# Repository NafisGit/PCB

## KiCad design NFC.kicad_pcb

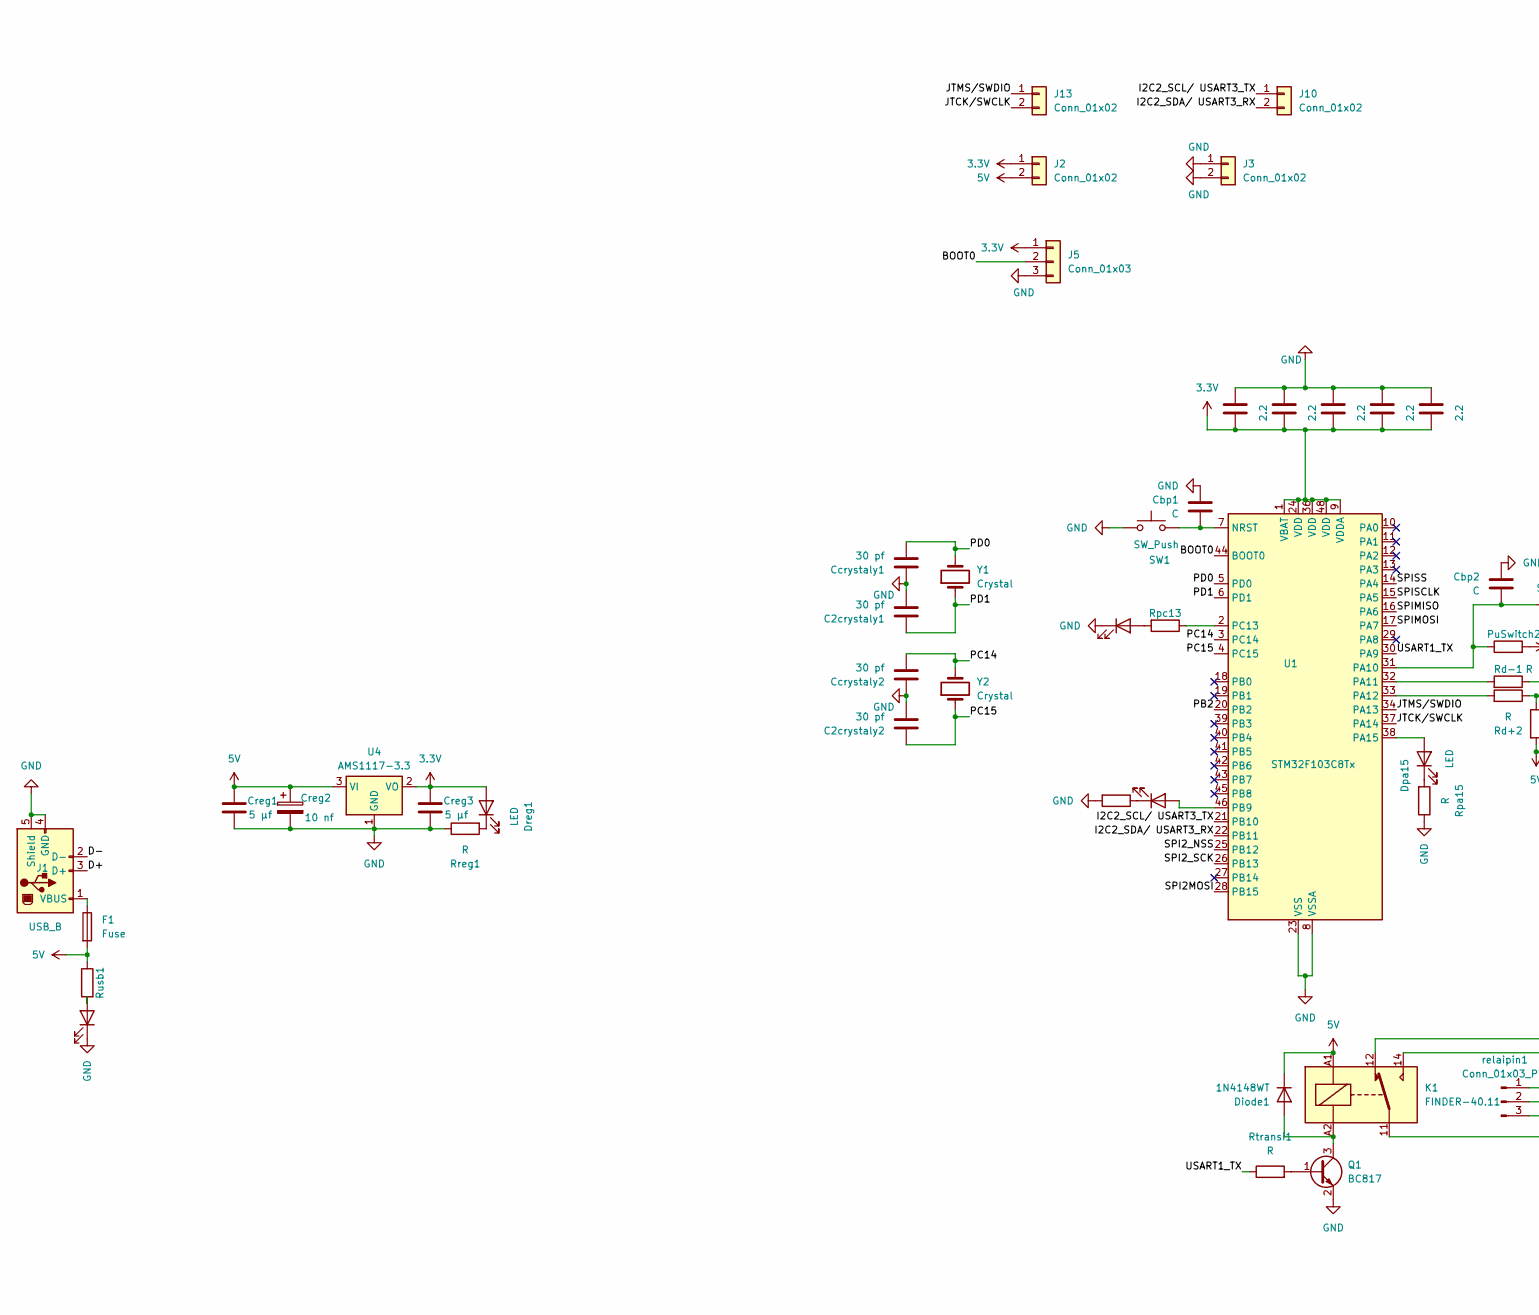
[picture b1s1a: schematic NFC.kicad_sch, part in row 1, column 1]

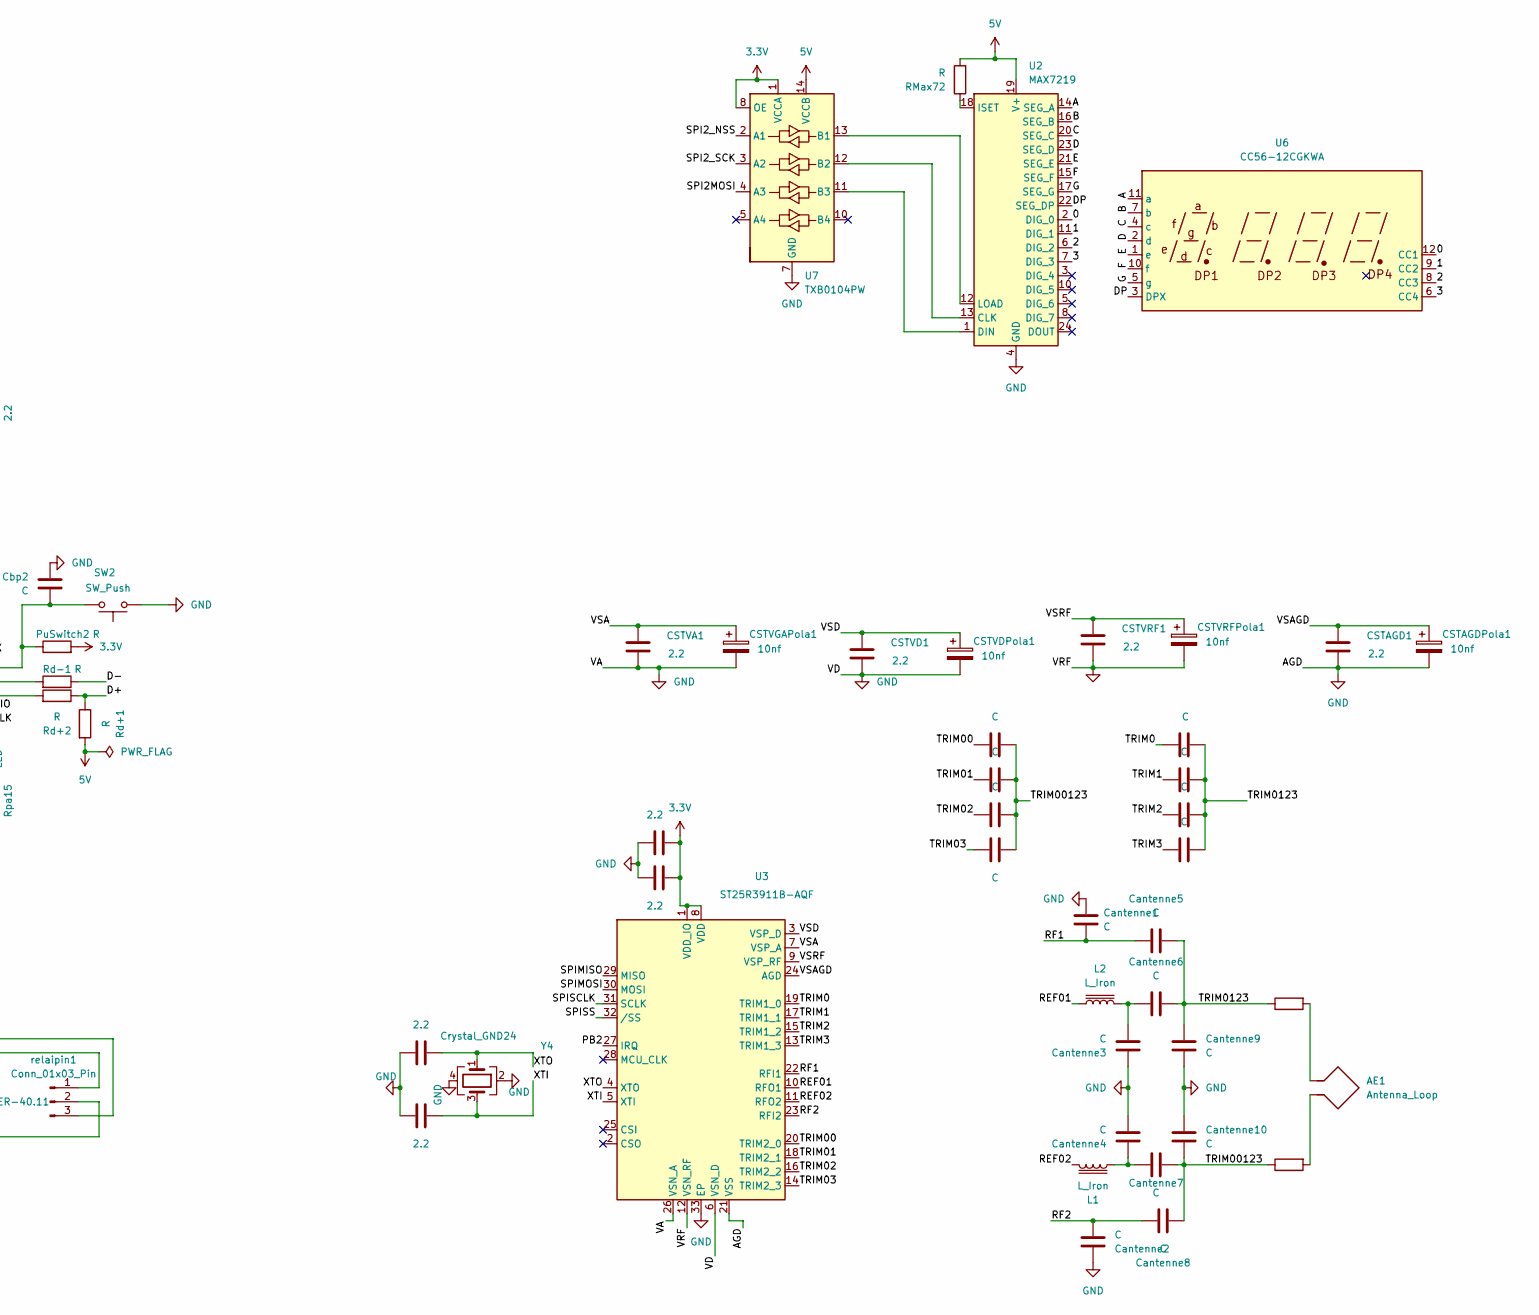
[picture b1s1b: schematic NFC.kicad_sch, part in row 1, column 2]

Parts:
AE1: Antenna_Loop; antenneNFClock
C2CrystalGND1: 2.2; C_0603_1608Metric_Pad1.08x0.95mm_HandSolder
C2crystaly1, C2crystaly2: 30 pf; C_0603_1608Metric_Pad1.08x0.95mm_HandSolder
CCrystalGND1: 2.2; C_0603_1608Metric_Pad1.08x0.95mm_HandSolder
CDecouplage1, CDecouplage2, CDecouplage3, CDecouplage4, CDecouplage5, CDecouplage7, CDecouplage8: 2.2; C_0603_1608Metric_Pad1.08x0.95mm_HandSolder
CSTAGD1: 2.2; C_0603_1608Metric_Pad1.08x0.95mm_HandSolder
CSTAGDPola1: 10nf; CP_Elec_5x5.3
CSTVA1: 2.2; C_0603_1608Metric_Pad1.08x0.95mm_HandSolder
CSTVD1: 2.2; C_0603_1608Metric_Pad1.08x0.95mm_HandSolder
CSTVDPola1: 10nf; CP_Elec_5x5.3
CSTVGAPola1: 10nf; CP_Elec_5x5.3
CSTVRF1: 2.2; C_0603_1608Metric_Pad1.08x0.95mm_HandSolder
CSTVRFPola1: 10nf; CP_Elec_5x5.3
CTRIM1, CTRIM2, CTRIM3, CTRIM4, CTRIM5, CTRIM6, CTRIM7: C; C_0603_1608Metric_Pad1.08x0.95mm_HandSolder
Cantenne1, Cantenne2, Cantenne3, Cantenne4, Cantenne5, Cantenne6, Cantenne7, Cantenne8, Cantenne9, Cantenne10: C; C_0603_1608Metric_Pad1.08x0.95mm_HandSolder
Cbp1, Cbp2: C; C_0603_1608Metric_Pad1.08x0.95mm_HandSolder
Ccrystaly1, Ccrystaly2: 30 pf; C_0603_1608Metric_Pad1.08x0.95mm_HandSolder
Creg1, Creg3: 5 µf; C_0603_1608Metric_Pad1.08x0.95mm_HandSolder
Creg2: 10 nf; C_0603_1608Metric_Pad1.08x0.95mm_HandSolder
Diode1: 1N4148WT; D_0805_2012Metric_Pad1.15x1.40mm_HandSolder
Dpa15: LED; LED_0603_1608Metric_Pad1.05x0.95mm_HandSolder
Dpb9: LED; LED_0603_1608Metric_Pad1.05x0.95mm_HandSolder
Dpc13: LED; LED_0603_1608Metric_Pad1.05x0.95mm_HandSolder
Dreg1: LED; LED_0603_1608Metric_Pad1.05x0.95mm_HandSolder
Dusb1: LED; LED_0603_1608Metric_Pad1.05x0.95mm_HandSolder
F1: Fuse; Fuse_1812_4532Metric_Pad1.30x3.40mm_HandSolder
J1: USB_B; USB_Micro-B_Molex_47346-0001
J2, J3, J10, J13: Conn_01x02; PinHeader_1x02_P2.54mm_Vertical
J5: Conn_01x03; PinHeader_1x03_P2.54mm_Vertical
K1: FINDER-40.11; Relay_SPDT_Finder_36.11
L1, L2: L_Iron; L_0805_2012Metric_Pad1.15x1.40mm_HandSolder
PuSwitch2: R; R_0603_1608Metric_Pad0.98x0.95mm_HandSolder
Q1: BC817; SOT-23
RMax72: R; R_0603_1608Metric_Pad0.98x0.95mm_HandSolder
Rantenne1, Rantenne2: R; R_0603_1608Metric_Pad0.98x0.95mm_HandSolder
Rd+1, Rd+2: R; R_0603_1608Metric_Pad0.98x0.95mm_HandSolder
Rd-1: R; R_0603_1608Metric_Pad0.98x0.95mm_HandSolder
Rpa15: R; R_0603_1608Metric_Pad0.98x0.95mm_HandSolder
Rpb9: R; R_0603_1608Metric_Pad0.98x0.95mm_HandSolder
Rpc13: R; R_0603_1608Metric_Pad0.98x0.95mm_HandSolder
Rreg1: R; R_0603_1608Metric_Pad0.98x0.95mm_HandSolder
Rtransi1: R; R_0603_1608Metric_Pad0.98x0.95mm_HandSolder
Rusb1: R; R_0603_1608Metric_Pad0.98x0.95mm_HandSolder
SW1, SW2: SW_Push; SW_SPST_SKQG_WithStem
TRIM1: C; C_0603_1608Metric_Pad1.08x0.95mm_HandSolder
U1: STM32F103C8Tx; LQFP-48_7x7mm_P0.5mm
U2: MAX7219; SOIC-24W_7.5x15.4mm_P1.27mm
U3: ST25R3911B-AQF; QFN-32-1EP_5x5mm_P0.5mm_EP3.6x3.6mm_ThermalVias
U4: AMS1117-3.3; SOT-223-3_TabPin2
U6: CC56-12CGKWA; 7 segments
U7: TXB0104PW; TSSOP-14_4.4x5mm_P0.65mm
Y1, Y2: Crystal; Crystal_SMD_5032-2Pin_5.0x3.2mm_HandSoldering
Y4: Crystal_GND24; Crystal_SMD_EuroQuartz_MJ-4Pin_5.0x3.2mm_HandSoldering
relaipin1: Conn_01x03_Pin; TerminalBlock_Phoenix_MKDS-1,5-3-5.08_1x03_P5.08mm_Horizont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

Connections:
3.3V: CDecouplage1.2, CDecouplage2.2, CDecouplage3.1, CDecouplage4.1, CDecouplage5.1, CDecouplage7.1, CDecouplage8.1, Creg3.1, Dreg1.2 (A), J2.1, J5.1, PuSwitch2.2, U1.1 (VBAT), U1.9 (VDDA), U1.24 (VDD), U1.36 (VDD), U1.48 (VDD), U3.1 (VDD_IO), U3.8 (VDD), U4.2 (VO), U7.1 (VCCA), U7.8 (OE); also elsewhere on the board
5V: Creg1.1, Creg2.1, Diode1.1 (K), F1.2, J2.2, K1.A1, RMax72.2, Rd+1.2, Rusb1.1, U2.19 (V+), U4.3 (VI), U7.14 (VCCB)
/0: U2.2 (DIG_0), U6.12 (CC1)
/1: U2.11 (DIG_1), U6.9 (CC2)
/2: U2.6 (DIG_2), U6.8 (CC3)
/3: U2.7 (DIG_3), U6.6 (CC4)
/ I2C2_SCL/ USART3_TX: J10.1, U1.21 (PB10)
/ I2C2_SDA/ USART3_RX: J10.2, U1.22 (PB11)
/A: U2.14 (SEG_A), U6.11 (a)
/B: U2.16 (SEG_B), U6.7 (b)
/BOOT0: J5.2, U1.44 (BOOT0)
/C: U2.20 (SEG_C), U6.4 (c)
/D: U2.23 (SEG_D), U6.2 (d)
/D+: J1.3 (D+), Rd+1.1, Rd+2.1
/D-: J1.2 (D-), Rd-1.1
/DP: U2.22 (SEG_DP), U6.3 (DPX)
/E: U2.21 (SEG_E), U6.1 (e)
/F: U2.15 (SEG_F), U6.10 (f)
/G: U2.17 (SEG_G), U6.5 (g)
/JTCK/SWCLK: J13.2, U1.37 (PA14)
/JTMS/SWDIO: J13.1, U1.34 (PA13)
/PB2: U1.20 (PB2), U3.27 (IRQ)
/PC14: Ccrystaly2.2, U1.3 (PC14), Y2.2
/PC15: C2crystaly2.1, U1.4 (PC15), Y2.1
/PD0: Ccrystaly1.2, U1.5 (PD0), Y1.2
/PD1: C2crystaly1.1, U1.6 (PD1), Y1.1
/REF01: L2.1, U3.10 (RFO1)
/REF02: L1.1, U3.11 (RFO2)
/RF1: Cantenne1.2, Cantenne5.1, U3.22 (RFI1)
/RF2: Cantenne2.2, Cantenne8.1, U3.23 (RFI2)
/SPI2MOSI: U1.28 (PB15), U7.4 (A3)
/SPI2_NSS: U1.25 (PB12), U7.2 (A1)
/SPI2_SCK: U1.26 (PB13), U7.3 (A2)
/SPIMISO: U1.16 (PA6), U3.29 (MISO)
/SPIMOSI: U1.17 (PA7), U3.30 (MOSI)
/SPISCLK: U1.15 (PA5), U3.31 (SCLK)
/SPISS: U1.14 (PA4), U3.32 (/SS)
/TRIM0: CTRIM4.1, U3.19 (TRIM1_0)
/TRIM00: CTRIM1.1, U3.20 (TRIM2_0)
/TRIM01: TRIM1.1, U3.18 (TRIM2_1)
/TRIM1: CTRIM5.1, U3.17 (TRIM1_1)
/TRIM2: CTRIM6.1, U3.15 (TRIM1_2)
/TRIM02: CTRIM2.1, U3.16 (TRIM2_2)
/TRIM3: CTRIM7.1, U3.13 (TRIM1_3)
/TRIM03: CTRIM3.1, U3.14 (TRIM2_3)
/TRIM00123: CTRIM1.2, CTRIM2.2, CTRIM3.2, Cantenne7.2, Cantenne8.2, Cantenne10.2, Rantenne2.1, TRIM1.2
/TRIM0123: CTRIM4.2, CTRIM5.2, CTRIM6.2, CTRIM7.2, Cantenne5.2, Cantenne6.2, Cantenne9.2, Rantenne1.1
/USART1_TX: Rtransi1.1, U1.30 (PA9)
/VSA: CSTVA1.1, CSTVGAPola1.1, U3.7 (VSP_A)
/VSAGD: CSTAGD1.1, CSTAGDPola1.1, U3.24 (AGD)
/VSD: CSTVD1.1, CSTVDPola1.1, U3.3 (VSP_D)
/VSRF: CSTVRF1.1, CSTVRFPola1.1, U3.9 (VSP_RF)
/XTI: C2CrystalGND1.2, U3.5 (XTI), Y4.3
/XTO: CCrystalGND1.2, U3.4 (XTO), Y4.1
GND: C2CrystalGND1.1, C2crystaly1.2, C2crystaly2.2, CCrystalGND1.1, CDecouplage1.1, CDecouplage2.1, CDecouplage3.2, CDecouplage4.2, CDecouplage5.2, CDecouplage7.2, CDecouplage8.2, CSTAGD1.2, CSTAGDPola1.2, CSTVA1.2, CSTVD1.2, CSTVDPola1.2, CSTVGAPola1.2, CSTVRF1.2, CSTVRFPola1.2, Cantenne1.1, Cantenne2.1, Cantenne3.2, Cantenne4.2, Cantenne9.1, Cantenne10.1, Cbp1.2, Cbp2.2, Ccrystaly1.1, Ccrystaly2.1, Creg1.2, Creg2.2, Creg3.2, Dpc13.1 (K), Dusb1.1 (K), J1.4 (GND), J1.5 (Shield), J3.1, J3.2, J5.3, Q1.2 (E), Rpa15.1, Rpb9.2, Rreg1.1, SW1.1, SW2.1, U1.8 (VSSA), U1.23 (VSS), U1.35 (VSS), U1.47 (VSS), U2.4 (GND), U2.9 (GND), U3.6 (VSN_D), U3.12 (VSN_RF), U3.21 (VSS), U3.26 (VSN_A), U3.33 (EP), U4.1 (GND), U7.7 (GND), Y4.2, Y4.4; also elsewhere on the board
unnamed: AE1.1, Rantenne1.2
unnamed: AE1.2, Rantenne2.2
unnamed: Cantenne3.1, Cantenne6.1, L2.2
unnamed: Cantenne4.1, Cantenne7.1, L1.2
unnamed: Diode1.2 (A), K1.A2, Q1.3 (C)
unnamed: Dpa15.2 (A), U1.38 (PA15)
unnamed: Dpa15.1 (K), Rpa15.2
unnamed: Dpb9.2 (A), U1.46 (PB9)
unnamed: Dpb9.1 (K), Rpb9.1
unnamed: Dpc13.2 (A), Rpc13.2
unnamed: Dreg1.1 (K), Rreg1.2
unnamed: Dusb1.2 (A), Rusb1.2
unnamed: F1.1, J1.1 (VBUS)
unnamed: Q1.1 (B), Rtransi1.2
unnamed: Cbp2.1, PuSwitch2.1, SW2.2, U1.31 (PA10)
unnamed: Rd-1.2, U1.32 (PA11)
unnamed: Rd+2.2, U1.33 (PA12)
unnamed: Rpc13.1, U1.2 (PC13)
unnamed: U2.13 (CLK), U7.12 (B2)
unnamed: U2.1 (DIN), U7.11 (B3)
unnamed: RMax72.1, U2.18 (ISET)
unnamed: U2.12 (LOAD), U7.13 (B1)
unnamed: K1.14, relaipin1.1
unnamed: K1.11, relaipin1.2
unnamed: K1.12, relaipin1.3

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
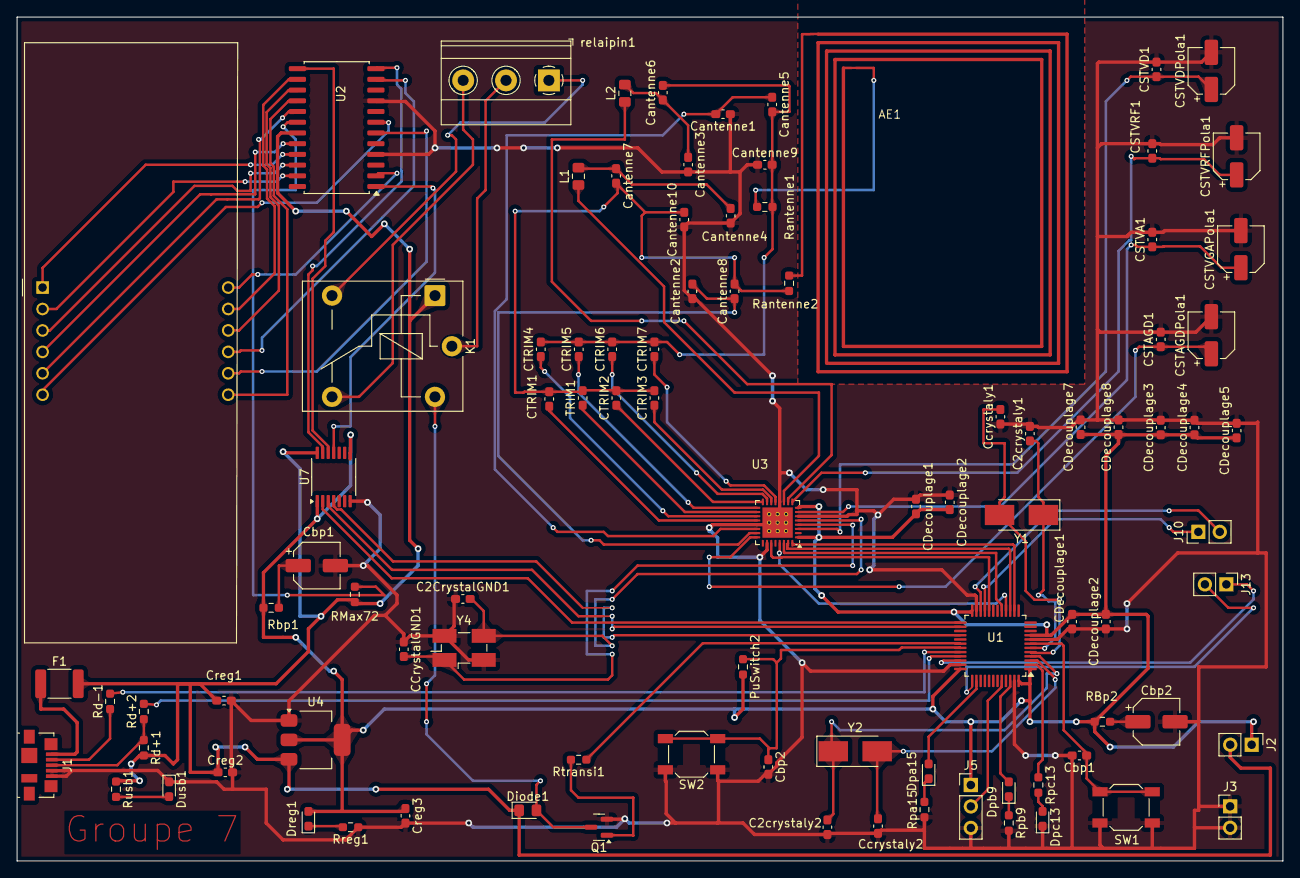
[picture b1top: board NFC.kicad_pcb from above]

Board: 2 copper layers, 150.0 x 100.0 mm, 93 parts (0 on the bottom side), 83 nets.

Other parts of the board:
CDecouplage1#2, CDecouplage2#2: 2.2; C_0603_1608Metric_Pad1.08x0.95mm_HandSolder
Cbp1#2: C; C_0603_1608Metric_Pad1.08x0.95mm_HandSolder
Cbp2#2: C; CP_Elec_5x5.3
RBp2: R; R_0603_1608Metric_Pad0.98x0.95mm_HandSolder
Rbp1: R; R_0603_1608Metric_Pad0.98x0.95mm_HandSolder

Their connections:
3.3V: CDecouplage1#2.2, CDecouplage2#2.2, RBp2.2, Rbp1.2; also elsewhere on the board
GND: CDecouplage1#2.1, CDecouplage2#2.1, Cbp1#2.2, Cbp2#2.2; also elsewhere on the board
unnamed: Cbp2#2.1, RBp2.1
